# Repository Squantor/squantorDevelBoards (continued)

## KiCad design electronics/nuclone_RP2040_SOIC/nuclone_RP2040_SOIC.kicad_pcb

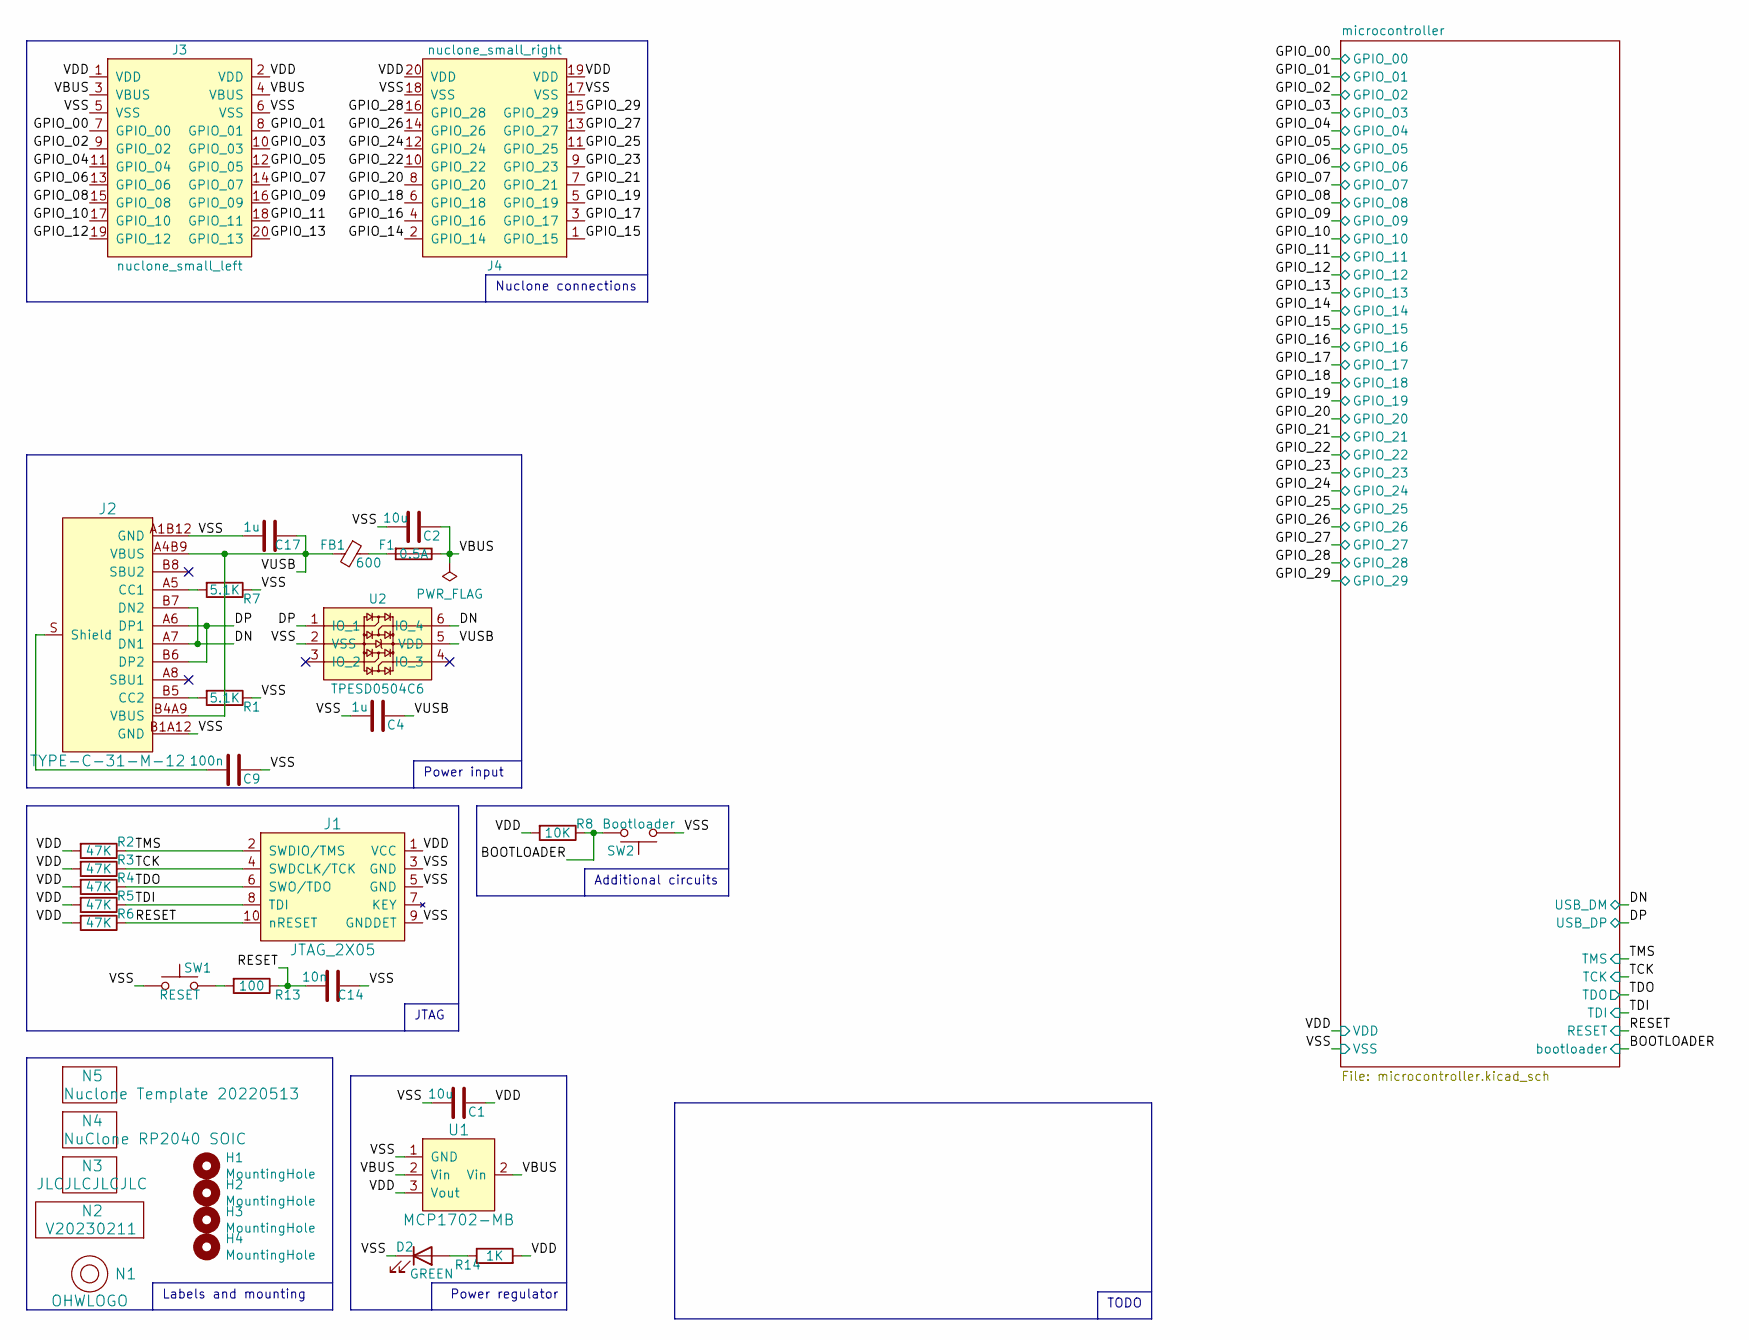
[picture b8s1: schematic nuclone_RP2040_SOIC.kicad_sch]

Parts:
C1, C2: 10u; C_0603
C4: 1u; C_0402
C9: 100n; C_0805
C14: 10n; C_0402
C17: 1u; C_0603
D2: GREEN; LED_0603_hand
F1: 0.5A; F_0603_hand
FB1: 600; L_0603
H1, H2, H3, H4: MountingHole; MountingHole_3.2mm_M3_Pad_Via
J1: JTAG_2X05; Header-0127-2X05-H006
J2: TYPE-C-31-M-12; USB-C-HRO-31-M-12
J3: nuclone_small_left; nuclone_small_left_stacked
J4: nuclone_small_right; nuclone_small_right_stacked
N1: OHWLOGO; OSHW-Symbol_6.7x6mm_SilkScreen
N2: V20230211; Label_Generic
N3: JLCJLCJLCJLC; Label_Generic
N4: NuClone RP2040 SOIC; Label_Generic
N5: Nuclone Template 20220513; Label_Generic
R1, R7: 5.1K; R_0402_hand
R2, R3, R4, R5, R6: 47K; R_0402_hand
R8: 10K; R_0402_hand
R13: 100; R_0402_hand
R14: 1K; R_0402_hand
SW1: RESET; TD-85XU
SW2: Bootloader; TD-85XU
U1: MCP1702-MB; SOT89-NXP
U2: TPESD0504C6; SOT363-ONsemi

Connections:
/BOOTLOADER: R8.1, SW2.2; also elsewhere on the board
/DN: J2.A7 (DN1), J2.B7 (DN2), U2.6 (IO_4); also elsewhere on the board
/DP: J2.A6 (DP1), J2.B6 (DP2), U2.1 (IO_1); also elsewhere on the board
/GPIO_00: J3.7 (GPIO_00); also elsewhere on the board
/GPIO_01: J3.8 (GPIO_01); also elsewhere on the board
/GPIO_02: J3.9 (GPIO_02); also elsewhere on the board
/GPIO_03: J3.10 (GPIO_03); also elsewhere on the board
/GPIO_04: J3.11 (GPIO_04); also elsewhere on the board
/GPIO_05: J3.12 (GPIO_05); also elsewhere on the board
/GPIO_06: J3.13 (GPIO_06); also elsewhere on the board
/GPIO_07: J3.14 (GPIO_07); also elsewhere on the board
/GPIO_08: J3.15 (GPIO_08); also elsewhere on the board
/GPIO_09: J3.16 (GPIO_09); also elsewhere on the board
/GPIO_10: J3.17 (GPIO_10); also elsewhere on the board
/GPIO_11: J3.18 (GPIO_11); also elsewhere on the board
/GPIO_12: J3.19 (GPIO_12); also elsewhere on the board
/GPIO_13: J3.20 (GPIO_13); also elsewhere on the board
/GPIO_14: J4.2 (GPIO_14); also elsewhere on the board
/GPIO_15: J4.1 (GPIO_15); also elsewhere on the board
/GPIO_16: J4.4 (GPIO_16); also elsewhere on the board
/GPIO_17: J4.3 (GPIO_17); also elsewhere on the board
/GPIO_18: J4.6 (GPIO_18); also elsewhere on the board
/GPIO_19: J4.5 (GPIO_19); also elsewhere on the board
/GPIO_20: J4.8 (GPIO_20); also elsewhere on the board
/GPIO_21: J4.7 (GPIO_21); also elsewhere on the board
/GPIO_22: J4.10 (GPIO_22); also elsewhere on the board
/GPIO_23: J4.9 (GPIO_23); also elsewhere on the board
/GPIO_24: J4.12 (GPIO_24); also elsewhere on the board
/GPIO_25: J4.11 (GPIO_25); also elsewhere on the board
/GPIO_26: J4.14 (GPIO_26); also elsewhere on the board
/GPIO_27: J4.13 (GPIO_27); also elsewhere on the board
/GPIO_28: J4.16 (GPIO_28); also elsewhere on the board
/GPIO_29: J4.15 (GPIO_29); also elsewhere on the board
/RESET: C14.2, J1.10 (nRESET), R6.1, R13.1; also elsewhere on the board
/TCK: J1.4 (SWDCLK/TCK), R3.1; also elsewhere on the board
/TDI: J1.8 (TDI), R5.1
/TDO: J1.6 (SWO/TDO), R4.1
/TMS: J1.2 (SWDIO/TMS), R2.1; also elsewhere on the board
/VBUS: C2.2, F1.1, J3.3 (VBUS), J3.4 (VBUS), U1.2 (Vin)
/VDD: C1.1, J1.1 (VCC), J3.1 (VDD), J3.2 (VDD), J4.19 (VDD), J4.20 (VDD), R2.2, R3.2, R4.2, R5.2, R6.2, R8.2, R14.2, U1.3 (Vout); also elsewhere on the board
/VSS: C1.2, C2.1, C4.2, C9.1, C14.1, C17.1, D2.1 (K), J1.3 (GND), J1.5 (GND), J1.9 (GNDDET), J2.A1B12 (GND), J2.B1A12 (GND), J3.5 (VSS), J3.6 (VSS), J4.17 (VSS), J4.18 (VSS), R1.1, R7.1, SW1.1, SW2.1, U1.1 (GND), U2.2 (VSS); also elsewhere on the board
/VUSB: C4.1, C17.2, FB1.2, J2.A4B9 (VBUS), J2.B4A9 (VBUS), U2.5 (VDD)
unnamed: C9.2, J2.S (Shield)
unnamed: D2.2 (A), R14.1
unnamed: F1.2, FB1.1
unnamed: J2.A5 (CC1), R7.2
unnamed: J2.B5 (CC2), R1.2
unnamed: R13.2, SW1.2

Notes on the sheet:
JTAG
Power regulator
TODO
Additional circuits
Nuclone connections
Labels and mounting
Power input

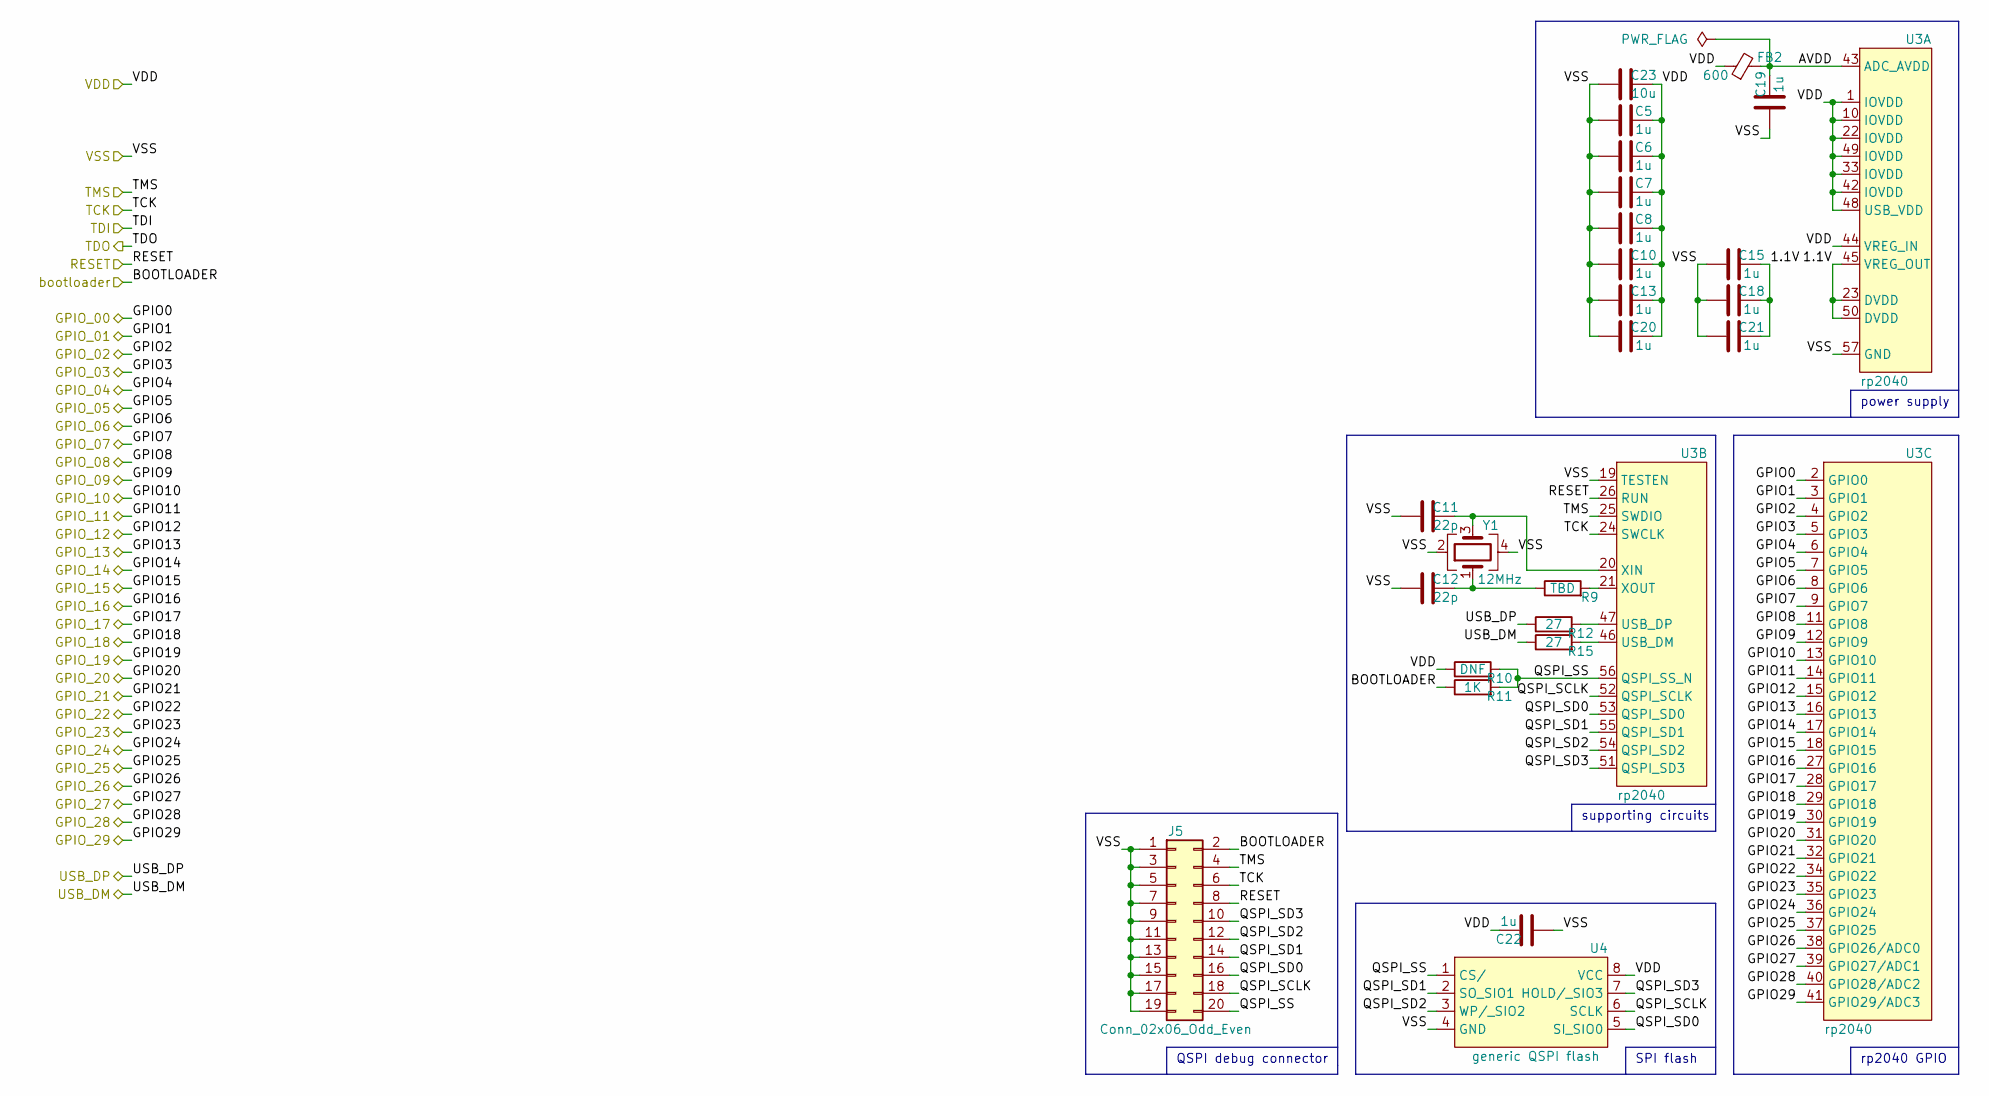
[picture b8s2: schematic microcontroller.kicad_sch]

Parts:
C5, C6, C7, C8, C10, C13, C15, C18, C19, C20, C21, C22: 1u; C_0402
C11, C12: 22p; C_0402
C23: 10u; C_0603
FB2: 600; L_0402
J5: Conn_02x06_Odd_Even; Header-0127-2X10-H006
R9: TBD; R_0402_hand
R10: DNF; R_0402_hand
R11: 1K; R_0402_hand
R12, R15: 27; R_0402_hand
U3: rp2040; QFN56_7by7mm_RaspberryPi
U4: generic QSPI flash; SOIC-8_dual_wide
Y1: 12MHz; Crystal_2520_4

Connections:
/BOOTLOADER: J5.2, R11.1; also elsewhere on the board
/DN: R15.1; also elsewhere on the board
/DP: R12.1; also elsewhere on the board
/GPIO_00: U3.2 (GPIO0); also elsewhere on the board
/GPIO_01: U3.3 (GPIO1); also elsewhere on the board
/GPIO_02: U3.4 (GPIO2); also elsewhere on the board
/GPIO_03: U3.5 (GPIO3); also elsewhere on the board
/GPIO_04: U3.6 (GPIO4); also elsewhere on the board
/GPIO_05: U3.7 (GPIO5); also elsewhere on the board
/GPIO_06: U3.8 (GPIO6); also elsewhere on the board
/GPIO_07: U3.9 (GPIO7); also elsewhere on the board
/GPIO_08: U3.11 (GPIO8); also elsewhere on the board
/GPIO_09: U3.12 (GPIO9); also elsewhere on the board
/GPIO_10: U3.13 (GPIO10); also elsewhere on the board
/GPIO_11: U3.14 (GPIO11); also elsewhere on the board
/GPIO_12: U3.15 (GPIO12); also elsewhere on the board
/GPIO_13: U3.16 (GPIO13); also elsewhere on the board
/GPIO_14: U3.17 (GPIO14); also elsewhere on the board
/GPIO_15: U3.18 (GPIO15); also elsewhere on the board
/GPIO_16: U3.27 (GPIO16); also elsewhere on the board
/GPIO_17: U3.28 (GPIO17); also elsewhere on the board
/GPIO_18: U3.29 (GPIO18); also elsewhere on the board
/GPIO_19: U3.30 (GPIO19); also elsewhere on the board
/GPIO_20: U3.31 (GPIO20); also elsewhere on the board
/GPIO_21: U3.32 (GPIO21); also elsewhere on the board
/GPIO_22: U3.34 (GPIO22); also elsewhere on the board
/GPIO_23: U3.35 (GPIO23); also elsewhere on the board
/GPIO_24: U3.36 (GPIO24); also elsewhere on the board
/GPIO_25: U3.37 (GPIO25); also elsewhere on the board
/GPIO_26: U3.38 (GPIO26/ADC0); also elsewhere on the board
/GPIO_27: U3.39 (GPIO27/ADC1); also elsewhere on the board
/GPIO_28: U3.40 (GPIO28/ADC2); also elsewhere on the board
/GPIO_29: U3.41 (GPIO29/ADC3); also elsewhere on the board
/RESET: J5.8, U3.26 (RUN); also elsewhere on the board
/TCK: J5.6, U3.24 (SWCLK); also elsewhere on the board
/TMS: J5.4, U3.25 (SWDIO); also elsewhere on the board
/VDD: C5.2, C6.2, C7.2, C8.2, C10.2, C13.2, C20.2, C22.2, C23.2, FB2.1, R10.1, U3.1 (IOVDD), U3.10 (IOVDD), U3.22 (IOVDD), U3.33 (IOVDD), U3.42 (IOVDD), U3.44 (VREG_IN), U3.48 (USB_VDD), U3.49 (IOVDD), U4.8 (VCC); also elsewhere on the board
/VSS: C5.1, C6.1, C7.1, C8.1, C10.1, C11.1, C12.1, C13.1, C15.1, C18.1, C19.1, C20.1, C21.1, C22.1, C23.1, J5.1, J5.3, J5.5, J5.7, J5.9, J5.11, J5.13, J5.15, J5.17, J5.19, U3.19 (TESTEN), U3.57 (GND), U4.4 (GND), Y1.2, Y1.4; also elsewhere on the board
/microcontroller/1.1V: C15.2, C18.2, C21.2, U3.23 (DVDD), U3.45 (VREG_OUT), U3.50 (DVDD)
/microcontroller/AVDD: C19.2, FB2.2, U3.43 (ADC_AVDD)
/microcontroller/QSPI_SCLK: J5.18, U3.52 (QSPI_SCLK), U4.6 (SCLK)
/microcontroller/QSPI_SD0: J5.16, U3.53 (QSPI_SD0), U4.5 (SI_SIO0)
/microcontroller/QSPI_SD1: J5.14, U3.55 (QSPI_SD1), U4.2 (SO_SIO1)
/microcontroller/QSPI_SD2: J5.12, U3.54 (QSPI_SD2), U4.3 (WP/_SIO2)
/microcontroller/QSPI_SD3: J5.10, U3.51 (QSPI_SD3), U4.7 (HOLD/_SIO3)
/microcontroller/QSPI_SS: J5.20, R10.2, R11.2, U3.56 (QSPI_SS_N), U4.1 (CS/)
unnamed: C11.2, U3.20 (XIN), Y1.3
unnamed: C12.2, R9.1, Y1.1
unnamed: R9.2, U3.21 (XOUT)
unnamed: R12.2, U3.47 (USB_DP)
unnamed: R15.2, U3.46 (USB_DM)

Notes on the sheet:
supporting circuits
power supply
QSPI debug connector
rp2040 GPIO
SPI flash

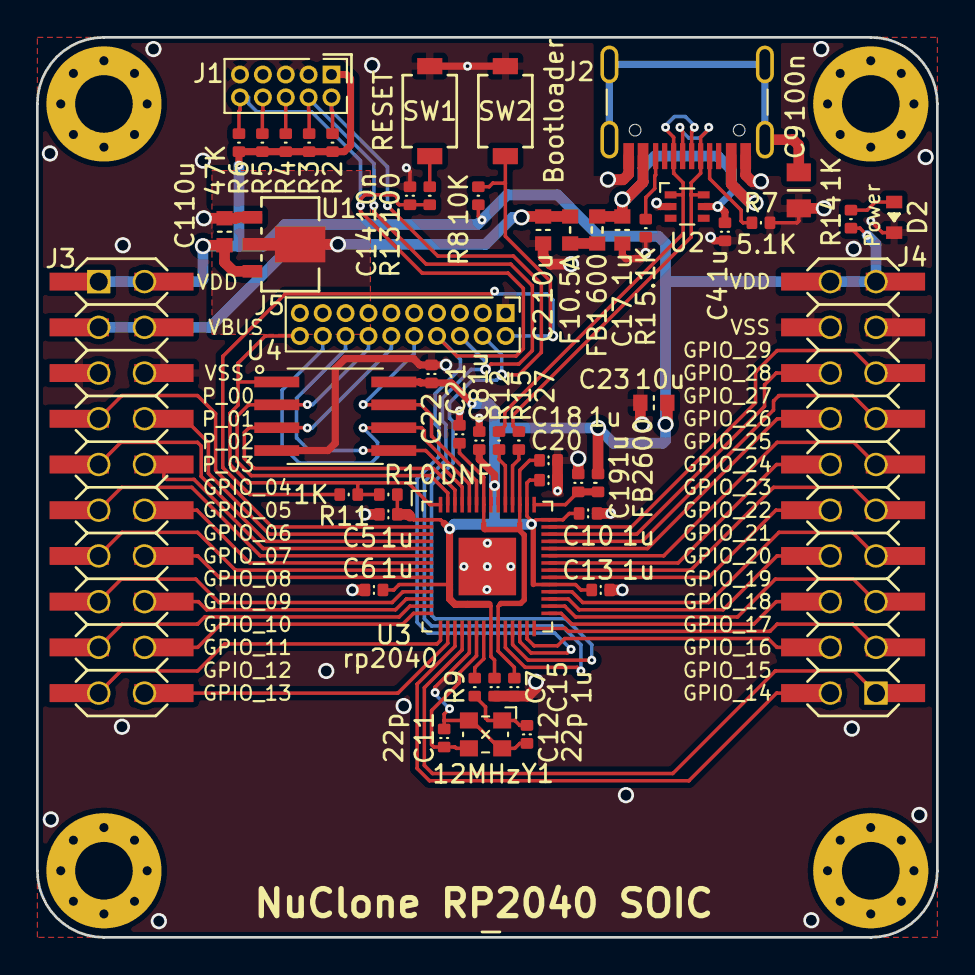
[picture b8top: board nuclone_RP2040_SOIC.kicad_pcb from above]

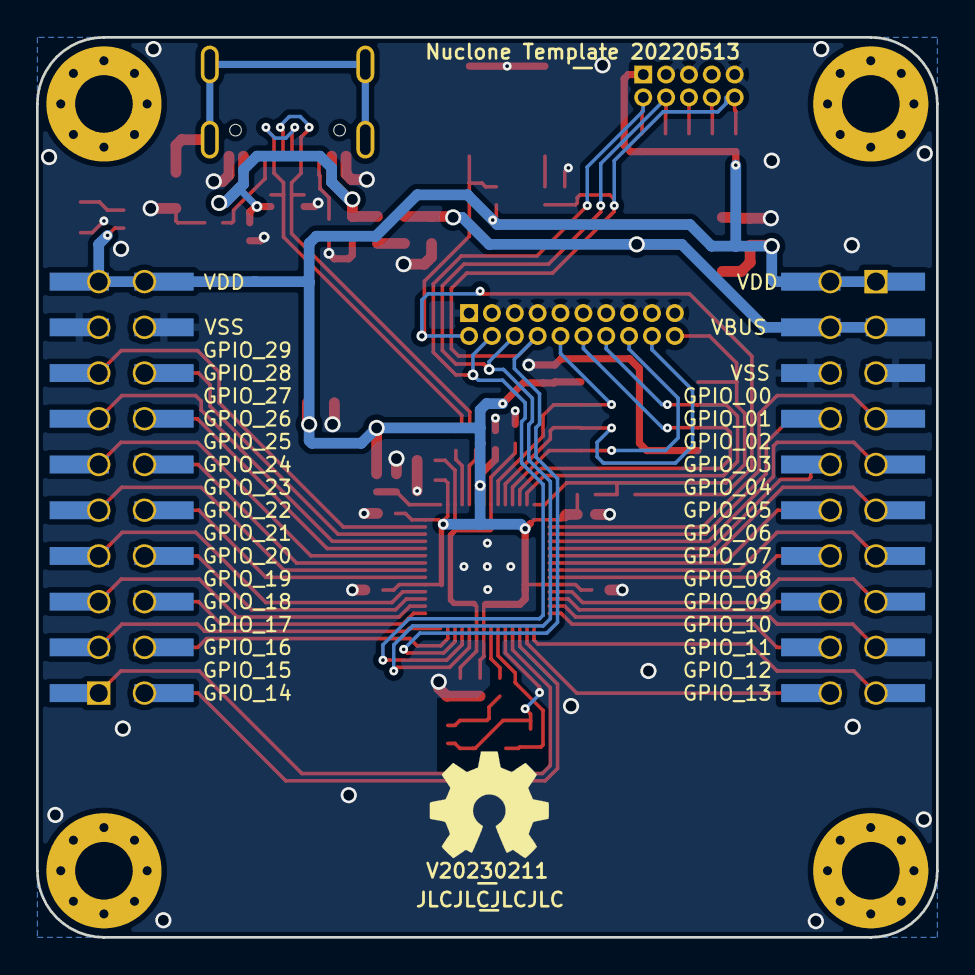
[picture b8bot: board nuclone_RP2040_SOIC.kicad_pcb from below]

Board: 4 copper layers, 50.0 x 50.0 mm, 61 parts (4 on the bottom side), 61 nets.

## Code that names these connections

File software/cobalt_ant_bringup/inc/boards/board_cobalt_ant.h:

/*
 * board_cobalt_ant.h
 *
 *  Created on: Dec 24, 2017
 *      Author: abilos
 */

#ifndef INC_BOARDS_BOARD_COBALT_ANT_H_
#define INC_BOARDS_BOARD_COBALT_ANT_H_

#include <chip.h>

// LED
#define LED_PORT	2
#define LED_PIN		9
#define LED_IOCON	IOCON_PIO2_9
// test pads (spare i/o's)
#define	TP1_PORT	0
#define	TP1_PIN		3
#define TP1_IOCON	IOCON_PIO0_3
#define	TP2_PORT	0
#define	TP2_PIN		6
#define TP2_IOCON	IOCON_PIO0_6
#define	TP3_PORT	2
#define	TP3_PIN		8
#define TP3_IOCON	IOCON_PIO2_8
#define	TP4_PORT	2
#define	TP4_PIN		5
#define TP4_IOCON	IOCON_PIO2_5
#define	TP5_PORT	3
#define	TP5_PIN		5
#define TP5_IOCON	IOCON_PIO3_5
#define	TP6_PORT	2
#define	TP6_PIN		6
#define TP6_IOCON	IOCON_PIO2_6
#define	TP7_PORT	2
#define	TP7_PIN		0
#define TP7_IOCON	IOCON_PIO2_0
// GPIO's
#define	GPIO1_PORT	0
#define GPIO1_PIN	2
#define GPIO1_IOCON	IOCON_PIO0_2
#define	GPIO2_PORT	1
#define GPIO2_PIN	8
#define GPIO2_IOCON	IOCON_PIO1_8
#define	GPIO3_PORT	0
#define GPIO3_PIN	5
#define GPIO3_IOCON	IOCON_PIO0_5
#define	GPIO4_PORT	0
#define GPIO4_PIN	4
#define GPIO4_IOCON	IOCON_PIO0_4
#define	GPIO5_PORT	2
#define GPIO5_PIN	7
#define GPIO5_IOCON	IOCON_PIO2_7
#define	GPIO6_PORT	1
#define GPIO6_PIN	9
#define GPIO6_IOCON	IOCON_PIO1_9
#define	GPIO7_PORT	2
#define GPIO7_PIN	2
#define GPIO7_IOCON	IOCON_PIO2_2
#define	GPIO8_PORT	2
#define GPIO8_PIN	3
#define GPIO8_IOCON	IOCON_PIO2_3
#define	GPIO9_PORT	2
#define GPIO9_PIN	1
#define GPIO9_IOCON	IOCON_PIO2_1
// FTDI serial
#define SERIAL_CTS_PORT	0
#define SERIAL_CTS_PIN	7
#define SERIAL_CTS_IOCON	IOCON_PIO0_7
#define SERIAL_RTS_PORT	1
#define SERIAL_RTS_PIN	5
#define SERIAL_RTS_IOCON	IOCON_PIO1_5
#define SERIAL_RXD_PORT	1
#define SERIAL_RXD_PIN	7
#define SERIAL_RXD_IOCON	IOCON_PIO1_7
#define SERIAL_TXD_PORT	1
#define SERIAL_TXD_PIN	6
#define SERIAL_TXD_IOCON	IOCON_PIO1_6
// SPI FLASH
#define FLASH_SCK_PORT	2
#define FLASH_SCK_PIN	11
#define FLASH_SCK_IOCON	IOCON_PIO2_11
#define FLASH_CE_PORT	2
#define FLASH_CE_PIN	10
#define FLASH_CE_IOCON	IOCON_PIO2_10
#define FLASH_MOSI_PORT	0
#define FLASH_MOSI_PIN	9
#define FLASH_MOSI_IOCON	IOCON_PIO0_9
#define FLASH_MISO_PORT	0
#define FLASH_MISO_PIN	8
#define FLASH_MISO_IOCON	IOCON_PIO0_8
// I2C breakout
// SPI breakout
//



void boardCobaltAntInit(void);



#endif /* INC_BOARDS_BOARD_COBALT_ANT_H_ */

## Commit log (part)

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2021-02-04 updated typos in LPC845 nuclone
2021-02-04 WIP layout of updated LPC812 nuclone
2021-02-04 small fixes
2021-02-04 WIP routing
2021-02-05 fixed error with the sizing of the box, there are two walls per box instead of one ;-)
2021-02-05 updated chamfer size of the close holes
2021-02-14 initial connector shrink to small nuclone
2021-02-14 updated STL files
2021-02-17 updated PCB library
2021-02-17 schematic updated
2021-02-18 fixed board label
2021-02-19 updated nuclone connectors
2021-02-19 minor changes and versionnumber update
2021-02-19 ERC passes, minor JTAG schematic updates
2021-02-19 changed PCB outline
2021-02-19 updated jumper labels
2021-02-19 completed layout/placement
2021-02-19 some more placement and silk improvements
2021-02-19 routing optimized
2021-02-19 minor silk improvements
2021-02-20 new footprints
2021-02-25 updated settings
2021-02-25 changed pin labels
2021-02-25 updated pin labels, plot outputs and plot dirs
2021-02-25 generated top paste layer for stencils
2021-03-06 newer PCB library with LPC845 QFP64
2021-03-19 updated software submodules
2021-03-19 updated buildsystem, more nice print output of the serial flash tester
2021-03-19 WIP board rename
2021-03-19 board rename completed
2021-03-19 integration with minunit
2021-03-19 updated license block
2021-03-22 initial addition of the LPC844 PQFP64 nuclone
2021-03-22 newer version of PCB library
2021-03-22 updated symbol tables
2021-03-22 added power led
2021-03-22 added power led and initial placement, removed old microcontroller
2021-03-22 forgot to commit component assignments
2021-03-29 updated versionnumber, added LQFP64 LPC845
2021-04-02 updated versionnumber, pinning, starting assigning pins
2021-04-02 assigned all pins, ERC passed
2021-04-02 started placing and routing
2021-04-03 WIP routing GPIO's and some SWD stuff
2021-04-03 fixed pinning on external GPIO port
2021-04-03 further routing of GPIO's
2021-04-04 updating labels
2021-04-04 updated library
2021-04-04 regenerated labels with new right connector
2021-04-05 small fix PQFP courtyards
2021-04-05 left connector label alignment
2021-04-05 updated PCB library, fixed PQFP64
2021-04-05 updated to fixed QFP package
2021-04-05 silk placement of component identifications
2021-04-05 renamed labels
2021-04-05 added copper keepout under crystal
2021-04-05 some track optimizations
2021-04-06 silk improvements
2021-04-25 applied fixed LPC84X QFP64
2021-04-25 updated versionnumber, changed via sizes, fixed VDD/VSS swap
2021-07-04 updated versionnumber, added USB-C connector
2021-07-04 added test points to SWD connections, added bootload button, removed series resistors of SWD
2021-07-04 imported components and ripping up old circuits, initial placement
2021-07-04 add RESET test pad
2021-07-04 changed design rules to be more in line with aisler
2021-07-04 footprint changes of buttons
2021-07-04 place and route done, time for silk placement
2021-07-05 switching component values to silk, minor placement updates
2021-07-05 updated versionnumber, silk changes, minor routing updates
2021-07-06 redrawn copper layers, updated plot output dir
2021-08-31 LPC812 version with USB-C
2021-08-31 updated libMcuLL
2021-08-31 submodule url changes and moves
2021-09-01 made it buildable again
2021-09-01 updated build environment
2021-09-01 updated to new minunit library
2021-09-03 added LPC844 blinky example to exercise display
2021-09-03 started with display connections and sending the first data
2021-09-03 WIP display functionality
2021-09-03 DONE: basic upcounting pattern on memory LCD
2021-09-04 more interesting pattern to show on display
2021-09-11 updated libEmbedded to have putpixel function
2021-09-11 changed sharp memory LCD demo to use the libEmbedded library
2021-09-11 added release build
2021-09-11 updated libc, updated descriptions
2021-09-12 small update
2021-09-15 fixed bug
2021-09-21 added crystal circuit
2021-09-21 modification on schematic symbol
2021-09-21 routing in progress
2021-09-23 moved some parts around, labeled PIO pins, silk placed bottom jumpers
2021-10-01 using flip command from lcd library
2021-10-26 changed USB C routing, updated versionnumber
2021-10-29 started with STM32F030 nuclone
2021-10-29 WIP schematic entry
2021-10-29 WIP routing and placing in progress
2021-10-30 additional routing and placing
2021-10-30 changed value of ferrite bead
2021-10-30 place and route done, WIP silk placement
2021-10-30 changed jumper label
2021-10-30 WIP silk placement, changing board pin labels
2021-10-31 copied F030 to F031 board
2021-11-04 updated LPC844 nuclone
2021-11-05 started with new nuclone board for 48pin STM32 controllers
2021-11-05 WIP schematic
2021-11-16 adding jumpers and some additional layout
2021-11-17 experimenting with stacking headers for nuclones
2021-11-21 added library
2021-11-21 updated stacked medium header
2021-11-23 improved routing
2021-11-23 changing to stacked header
2021-11-23 ported nuclone to using stacked headers
2021-11-24 updated LPC812 to different right connector pinning
2021-11-25 routed the new pinout
2021-11-25 changed header and ordering
2021-11-25 WIP STM32F030C8T6
2021-12-01 matching board with template
2021-12-01 added crystals to board
2021-12-02 further routing and placing of parts
2021-12-02 adding changes for production
2021-12-02 forgotten keepout
2022-02-23 updated nuclone to new template
2022-02-23 routed and changed pinning
2022-02-23 updates on routing
2022-02-23 removing old nuclone
2022-02-25 updated to newer nuclone template
2022-02-28 further changes
2022-03-01 routing completed silk placement in progress
2022-03-01 small routing and silk placement updates
2022-03-02 updated versionnumber, silk placement changed
2022-03-02 jumper silk placed
2022-03-02 updated jumper footprints
2022-03-03 fixed DRC error, updated versionnumber
2022-03-03 updated jumper labels and added keepout zone
2022-03-03 updated labels, added keepout, added AVCC/AVSS jumpers
2022-03-04 fixed labels
2022-03-06 added small uart nuclone
2022-03-06 updated versionnumber, added activity led
2022-03-10 plotted pcb
2022-03-10 plotted gerbers and small trace update
2022-04-18 added nuclone LPC804 and updated pcb library
2022-04-18 started schematic LPC804 nuclone
2022-04-19 fleshing out microcontroller subschematic
2022-04-19 WIP place and route
2022-04-24 updated label
2022-04-24 updated label and further routing
2022-04-26 routing completed, silk placement completed
2022-04-26 updated pin labels
2022-05-07 updating libraries to kicad 6
2022-05-07 removing old projects
2022-05-07 updated to kicad 6
2022-05-07 removing kicad 5 files
2022-05-07 fixed wrong labels
2022-05-07 updated footprints and relabeling things
2022-05-15 started initial RP2040 board
2022-05-25 WIP RP2040 definitions
2022-05-27 WIP: added schematic component and started defining schematic
2022-05-29 conversion to kicad 6.0
2022-05-29 conversion to kicad 6
2022-05-29 updated 3dmodel footprints of IC
2022-05-29 updated missing footprint
2022-05-29 WIP placing
2022-05-30 fixed pinout labels
2022-05-30 added QSPI flash
2022-05-30 added kicad 6 backups to ignore
2022-05-30 added serial flash
2022-07-04 further routing, added a QSPI debug connector for easy probing with logic analyser
2022-07-07 more alignment to official schematic
2022-07-10 updated crystal, further placing and routing
2022-07-11 harmonized schematic with application note
2022-07-11 reorganising some bits and pieces
2022-07-12 removed testpads and added debugging connector
2022-07-12 removed unneeded parts
2022-07-12 completed placing and routing
2022-07-13 switched SWD testpoints to pinheader
2022-07-13 placed and routed new connector
2022-07-13 further routing optimizations
2022-08-15 switched from testpins to debug connector
2022-08-19 changed test points to a connector for logic analyser
2022-08-19 rerouted debug connector
2022-08-19 no idea why this has changed
2022-09-12 reviewed
2022-09-16 updated silk and some traces
2022-12-04 updated small nuclone protoboard with usb 2 serial converter
2022-12-04 added nuclone small serial expansion
2022-12-04 schematic entry completed, ERC passes with few exceptions
2022-12-04 WIP placing silk screen items
2023-01-28 changed QSPI debug connector pinout
2023-01-28 changed solderpaste aperature size
2023-01-28 changed TCK to pullup instead of pulldown
2023-01-28 preparing to move all VDD nets to another layer so we can change all planes to ground planes
2023-01-29 updated PCB with newer QFN package
2023-01-29 made all planes ground only planes, added and fleshed out netclasses
2023-01-29 updated usb connector to non warning version
2023-01-29 renamed RP2040 nuclone with SON flash
2023-01-29 copied RP2040 to create different variants
2023-01-29 placed, routed and checked WSON nuclone variant
2023-01-29 missed save
2023-01-31 started nuclone RP2040 using a raspberry pi pico
2023-02-05 ERC passes without errors, DRC without errors and warnings, updated versionnumber
2023-02-05 fixed SOIC RP2040 nuclone errors
2023-02-06 fixed DRC errors, updated versionnumber
2023-02-06 updated 0402 and 0603 components, added crystal ground plane keepout
2023-02-07 small updates
2023-02-07 updated SON RP2040 nuclone
2023-02-11 some save
2023-02-11 final check, updated versionnumber
2023-02-11 updated versionnumber, fixed silk positioning
2023-02-21 WIP schematic definition
2023-02-23 added more levelshifters
2023-02-23 further routing and silk placement
2023-07-17 added a few planned small nuclone expansions
2023-07-17 WIP defining schematic for the small libmcull tester
2023-07-18 work in progress on small libmcull tester, removed clocking test too
2023-07-20 added more GPIO tests, silk placement
2023-07-22 WIP schematic definition of MCP355X evaluator
2023-07-22 WIP schematic, added breadboard, initial placement
2023-07-23 placing and silk placement
2023-08-01 added Voltage reference, placed and routed
2023-09-11 changing testpoints to headers
2023-09-13 changed all testpoints to headers for easier connections
2023-09-13 fixed DRC/ERC
2023-09-15 reviewed and small modifications
2023-12-03 updated changes and library
2023-12-13 applied aisler simple rules
2024-01-14 initial nuclone with raspberry pi pico fitted
2024-01-14 added pi pico footprints
2024-01-14 WIP place and route of the board
2024-01-14 place and routing done
2024-02-03 removed old controller
2024-02-03 created nuclone with pi pico and a USB-C connection
2024-02-03 added USB-C connection, routing and placing bits and pieces
2024-02-04 minor additions
2024-02-11 updated pinout to match the RP2040 nuclone
2024-02-11 small updates to newer fields
2024-02-11 changing pinouts to match RP2040 nuclone
2024-02-11 small trace updates
2024-02-16 updated to newer version
2024-02-18 added nuclone using aliexpress RP2040 module
2024-02-18 updated board description label
2024-02-18 prepping for production, updated footprint and versionnumber
2024-02-18 preparing for production, updated footprints and versionnumber, redrawn copper layers
2024-02-18 prepared for production, updated versionnumber and components
2024-03-08 moved RP2040 module so it does not collide with SWD/JTAG connector
2024-03-15 updated small libmcu tester
2024-04-22 moving small nuclone libmcull tester
2024-04-24 reviewed and small fixes
2024-04-26 preparing for production final checks
2024-06-07 updates to newer version
2024-06-07 added initial nuclone LPC804 TSSOP24 variant
2024-06-09 started LPC845 small version
2024-06-10 schematic further added
2024-06-12 added usb to serial converter in schematic and placed on PCB
2024-06-22 updated labels
2024-06-24 added medium LPC845 nuclone
2024-06-26 small routing and updated jumpers
2024-06-28 labels done, keepout around crystal
2024-06-28 updated versions, fixed DRC's
2024-06-28 minor changes
2024-06-29 added boot button jumper
2024-07-05 fixed ERC error
2024-07-07 fixed DRC errors and verified everything
2024-07-07 added crystal oscillator
2024-07-07 easier to solder crystal
2024-07-12 prepped for production with updated versionnumbers and some minor changes
